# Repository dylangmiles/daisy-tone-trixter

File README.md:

# Tone Trixter — Daisy Seed3

A guitar pedal that makes a piezo pickup sound like a studio microphone — in real time.

**Build log & demos:** [dylangmiles.github.io/tone-trixter](https://dylangmiles.github.io/tone-trixter/)

Piezo pickups are cheap and reliable but have a characteristic harsh, nasal "quack" that EQ alone
can't fix. Tone Trixter applies an **acoustic body impulse response** to the live piezo signal using
FFT convolution, transforming it to match a condenser microphone placed in front of the same guitar.

**Status: the active development path.** The pedal plays — guitar in, DSP chain, SD-loaded IR,
backing tracks, tuner and OLED menu all running on hardware from a 9 V supply. New work happens
here; the [RP2350 build](https://github.com/dylangmiles/pico-tone-trixter) is the V1 prototype that
proved the idea and is still gigging.

---

## Why the Seed3

The V1 measurements kept arriving at the same conclusion: **the analogue front end sets the noise
floor**, not the DSP. The RP2350 build's ES8388 codec was itself a meaningful part of the noise
budget, which made that conclusion hard to test cleanly.

The Seed3's TAC5242 is 32-bit / 192 kHz with a −120 dB floor. The codec effectively stops being a
factor, and the front-end buffer becomes the *only* thing that matters for noise — which is exactly
the question this project turns on. The 480 MHz Cortex-M7 is a bonus rather than the reason.

---

## Hardware

**Processor:** Electrosmith Daisy Seed3 — STM32H750, Cortex-M7 @ 480 MHz, hardware FPU, 64 MB SDRAM
**Codec:** TI TAC5242 — 32-bit / 192 kHz, −120 dB noise floor, hardware-strapped

```
Guitar piezo → buffer daughter board (JFET follower, or OPA1642 op-amp)
  → Seed3 ADC
    → 2048-tap IR convolution (inline) → input trim → 3-band EQ
      → compressor/limiter → output level
    → backing-track mix (after the chain, deliberately)
  → Seed3 DAC → PA / headphones / interface
```

The piezo buffer lives on a swappable 5-pin daughter board, shared with the V1 build. ⚠ **The Seed3
has no input buffer of its own** and its input is line-level, so the high-impedance buffer stage is
mandatory rather than optional.

Built on cut-down perfboard with the Seed under-mounted, 9 V jack power, SH1106 OLED + rotary
encoder, two footswitches (tuner / DSP bypass), and a bit-banged microSD slot.

---

## Features

- **2048-tap IR convolution**, running inline on the M7 — no second core needed
- **DSP chain:** input trim → 3-band EQ (RBJ biquads) → compressor/limiter → output level
- **Presets** bundling all parameters plus IR selection; switching guitars re-stages the whole chain
- **SD card:** drop `tonetrix/` on a card to override presets (`presets.txt`) and add IRs
  (`ir/*.wav`) without reflashing
- **Backing tracks** streamed from the card, mixed *after* the chain so the bed never goes through
  the guitar's IR, EQ or compressor
- **YIN tuner**, full-screen, footswitch-toggled, muting, fed from the raw input
- **OLED home screen:** preset, IR, CPU load, and in / gain-reduction / out meters with a sticky
  clip indicator
- **Live USB-serial control:** every parameter adjustable while playing (`help` lists commands),
  plus timing, CPU and encoder diagnostics

⚠ **Boot is complete passthrough by design.** The pedal always starts transparent, so anything
measured at boot reflects the front end alone with no DSP on top — which matters while the analogue
path is still being characterised.

---

## Measured performance

Steady state, 48 kHz, 64-sample blocks, chain + 2048-tap IR engaged:

| Figure | Reading |
|---|---|
| Audio CPU, bypass | 1 % |
| Audio CPU, chain + IR | **16 % avg, 45 % peak** |
| Foreground loop | 6.6 ms worst, 8 ms period |
| Backing ring | 98–99 %, 0 underruns |
| Block latency | 1.33 ms |

⚠ **Two budgets, and only one is tight.** Audio has ~84 % spare — the foreground is the constrained
side, where a full OLED flush costs ~28 ms. Any optimisation belongs there, not in the audio path.

---

## Build and flash

Requires the ARM GCC toolchain, `dfu-util`, and [libDaisy](https://github.com/electro-smith/libDaisy)
+ [DaisySP](https://github.com/electro-smith/DaisySP).

```sh
make                                          # or: make LIBDAISY_DIR=/path/to/libDaisy
make program-boot                             # ONCE — installs the Daisy bootloader
make program-dfu                              # thereafter
screen /dev/tty.usbmodem* 115200              # console
```

⚠ **libDaisy must be the `seed3-updates` branch, pinned to a commit.** Seed3 support is not on
`main` — a stock libDaisy configures the wrong codec, and an unmerged branch can be force-pushed
underneath you.

⚠ **`APP_TYPE = BOOT_SRAM`.** The STM32H750 has only 128 KB of internal flash and this app does not
fit; it runs from 480 KB of internal SRAM via the Daisy bootloader, which is why `make program-boot`
is a required one-time step.

---

## Notes worth knowing before you read the code

Several things here deliberately do *not* use the obvious library call. Each has a measured reason,
documented at the point of use:

- **Our own SH1106 driver.** libDaisy's OLED transport sends one I²C transaction *per byte* — about
  77 ms per frame. Ours writes a page per transaction and sends only pages that changed.
- **Our own quadrature decode.** libDaisy's `Encoder::Increment()` needs one exact sample pattern
  that a detented PEC11R rarely produces; it works only within a narrow band of turn speeds.
- **Bit-banged SD over SPI.** The Daisy's SDMMC `CMD` pin is wired to ground on this layout, and the
  breakout's pin order matches no hardware SPI instance.
- **`-u _printf_float` in the Makefile.** libDaisy links `--specs=nano.specs`, and newlib-nano omits
  floating-point conversion from `printf` — every `%f` silently prints nothing without it.

`CLAUDE.md` carries the full engineering detail, including the hardware gotchas that cost bench time.

---

## Relationship to the RP2350 build

The two pedals share the analogue front end, the DSP chain design, the IR capture method, and **one
physical SD card** — the card layout lives once, in the
[Pico repo](https://github.com/dylangmiles/pico-tone-trixter), and both firmwares read it.

Driver sources that could reasonably be shared are kept byte-identical between the builds behind
small platform shims, so a protocol or layout fix on either platform applies to both.

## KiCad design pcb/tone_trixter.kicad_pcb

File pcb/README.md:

# Tone Trixter PCB — rev A

KiCad 10 project. **The schematic is GENERATED**: edit `tools/gen_schematic.py`, run it, never hand-edit
`tone_trixter.kicad_sch` (the next run overwrites it). Design intent and every value's reason are in
`private/docs/daisy_pcb_brief_2026-09-16.md`; pin numbers come from `../board.h`.

```
tools/gen_schematic.py          # the source of truth for the schematic
tools/kisch.py, tools/kisym.py  # tiny writer + KiCad-library symbol extractor
tone_trixter.kicad_sch          # generated
tone_trixter.kicad_pro          # project (created once)
TT.kicad_sym, sym-lib-table     # the Daisy Seed3 symbol, built from the pinout CSV
out/schematic.pdf               # review print (netlist.net + 1:1 board prints also in out/)
```

Check: `kicad-cli sch erc tone_trixter.kicad_sch` (only "symbol differs from library" notices expected —
the op-amp and SD symbols are flattened copies) and `kicad-cli sch export netlist`. `gen_schematic.py`
also runs a wire-through-pin check and prints `CHECK:` lines if any wire crosses a pin it should not.

## Layout (started 2026-10-09)

⚠ **`../enclosure/enclosure.py` is the SINGLE SOURCE OF TRUTH for panel-part positions** (2026-10-12;
enclosure tooling moved to a sibling `enclosure/` dir 2026-10-31). The paper template
(`../enclosure/tools/gen_template.py`) imports it, so the template and the board **cannot drift** —
change a position once, re-render, both follow. Convention locked there: **INPUT on the RIGHT,
OUTPUT on the LEFT** (signal R→L), encoder right of the centred screen.

The enclosure mock-up revised the brief's board envelope. **Current geometry** (see
`../enclosure/enclosure.py`, `../enclosure/tools/gen_template.py` + `gen_side_elevation.py`, rendered
in `../enclosure/out/`):

- 1590XX **landscape** (internal top-face plane 138 × 114, **2.33 mm walls**, internal cavity **33 mm**
  tall, Ø7 corner bosses). All measured off the box 2026-10-10.
- **Full-width board ~132 × 57 mm**, hugging the **back wall**, rear corners notched **10 × 10** for the
  bosses (Ø7 post → 3 mm play). Mounted high under the top face (**gap 8.24 mm**, set by the OLED glass
  flush + encoder body clearing); **Seed hangs ~16.5 below**; OLED + encoder reach up (screen centred on
  the board, toward the rear); footswitches panel-mounted up front at 90 mm centres.
- **TRS + DC jacks bottom-mounted** (barrel 12.4 below the board → axis **~33 % up the wall, lower
  third**, z ≈ 10.8), legs up through the PCB, isolated plastic bushings. **USB = Seed's own port** on a
  flexible extender. **Two high-Z inputs drilled in v1** — IN A (AIN1) + IN B (AIN2), both K3599 TRS;
  the XLR mic reserve is dropped (a v2 board).
- ✅ All Z-stack heights (OLED/encoder/Seed/jack/cavity) **measured** 2026-10-10; see the side-elevation.
- The mock-up is an **OUTSIDE drilling template** (tape outside, ink up, drill from outside; register by
  the box **centre** — mark the diagonals). The rear-wall strip is **mirrored** (drawn as seen from
  behind the pedal). For board-mounted jacks the most accurate method is to drill through the finished board.

**Assembly plan (decided 2026-10-15):** **0805** passives (kept over 0603 for hand-reworkability).
**JLC assembles the SMD** — **single-side on B.Cu** (all 112 SMDs under the board — bottom-lid
debug access; validated 0 on F.Cu 2026-10-31), prefer JLC Basic parts (small
Extended fee for the OPA1642 etc.); parts are LCSC-coded in `gen_schematic.py`. **Hand-solder the
through-hole** — jacks, encoder, Seed, footswitch/battery/DC connectors, test points. For the order,
export Gerbers + BOM + CPL from KiCad. Finish = **ENIG** (flatter pads for assembly). See brief §4.

**The outline is GENERATED** — `tools/gen_board.py` (run with KiCad's bundled python; has `pcbnew`):

```
/Applications/KiCad/KiCad.app/Contents/Frameworks/Python.framework/Versions/Current/bin/python3 \
    tools/gen_board.py          # writes tone_trixter.kicad_pcb: Edge.Cuts outline + M3 holes only
```

Then in KiCad: open `tone_trixter.kicad_pcb`, **Tools → Update PCB from Schematic (F8)** to pull in
the 102 footprints (the schematic has them all assigned), place per the mock-up, route, DRC, 3D-check
against the box height, Gerbers. One plane (bottom pour), star at power entry; no copper within 1 mm
of the edge; mounting holes become plane-bonded once the enclosure bond is finalised.

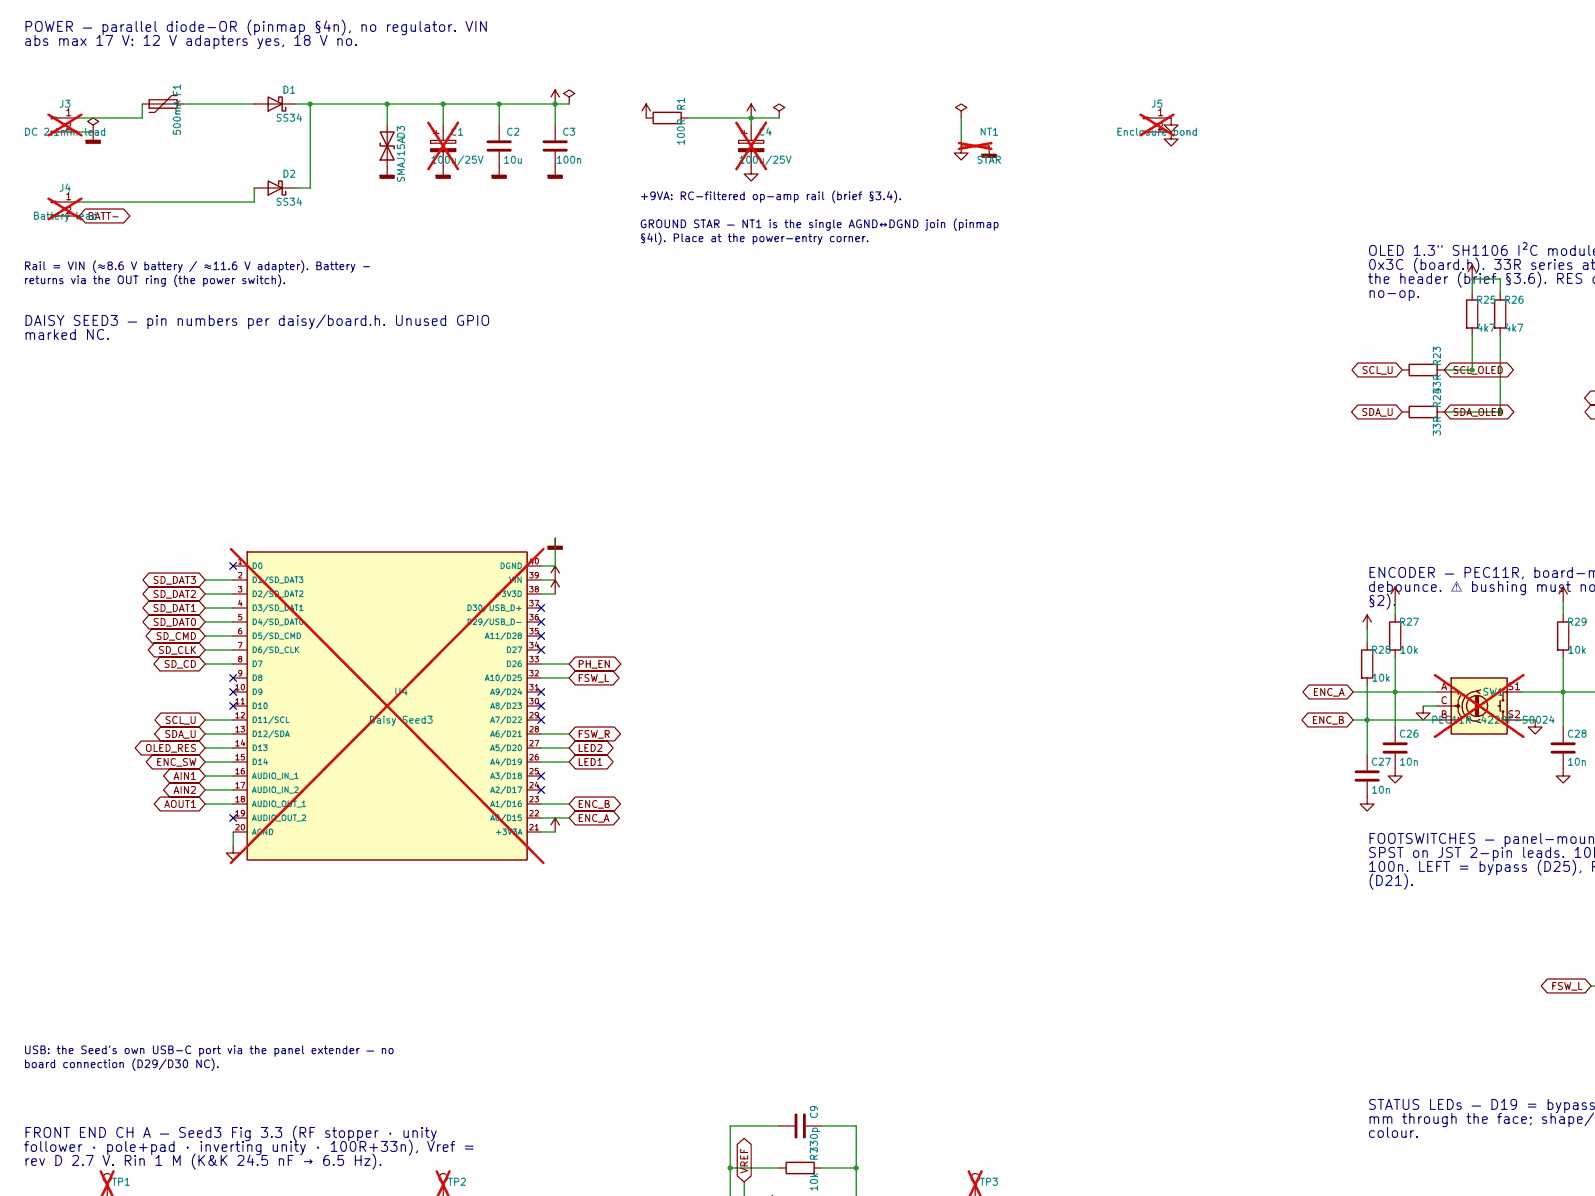
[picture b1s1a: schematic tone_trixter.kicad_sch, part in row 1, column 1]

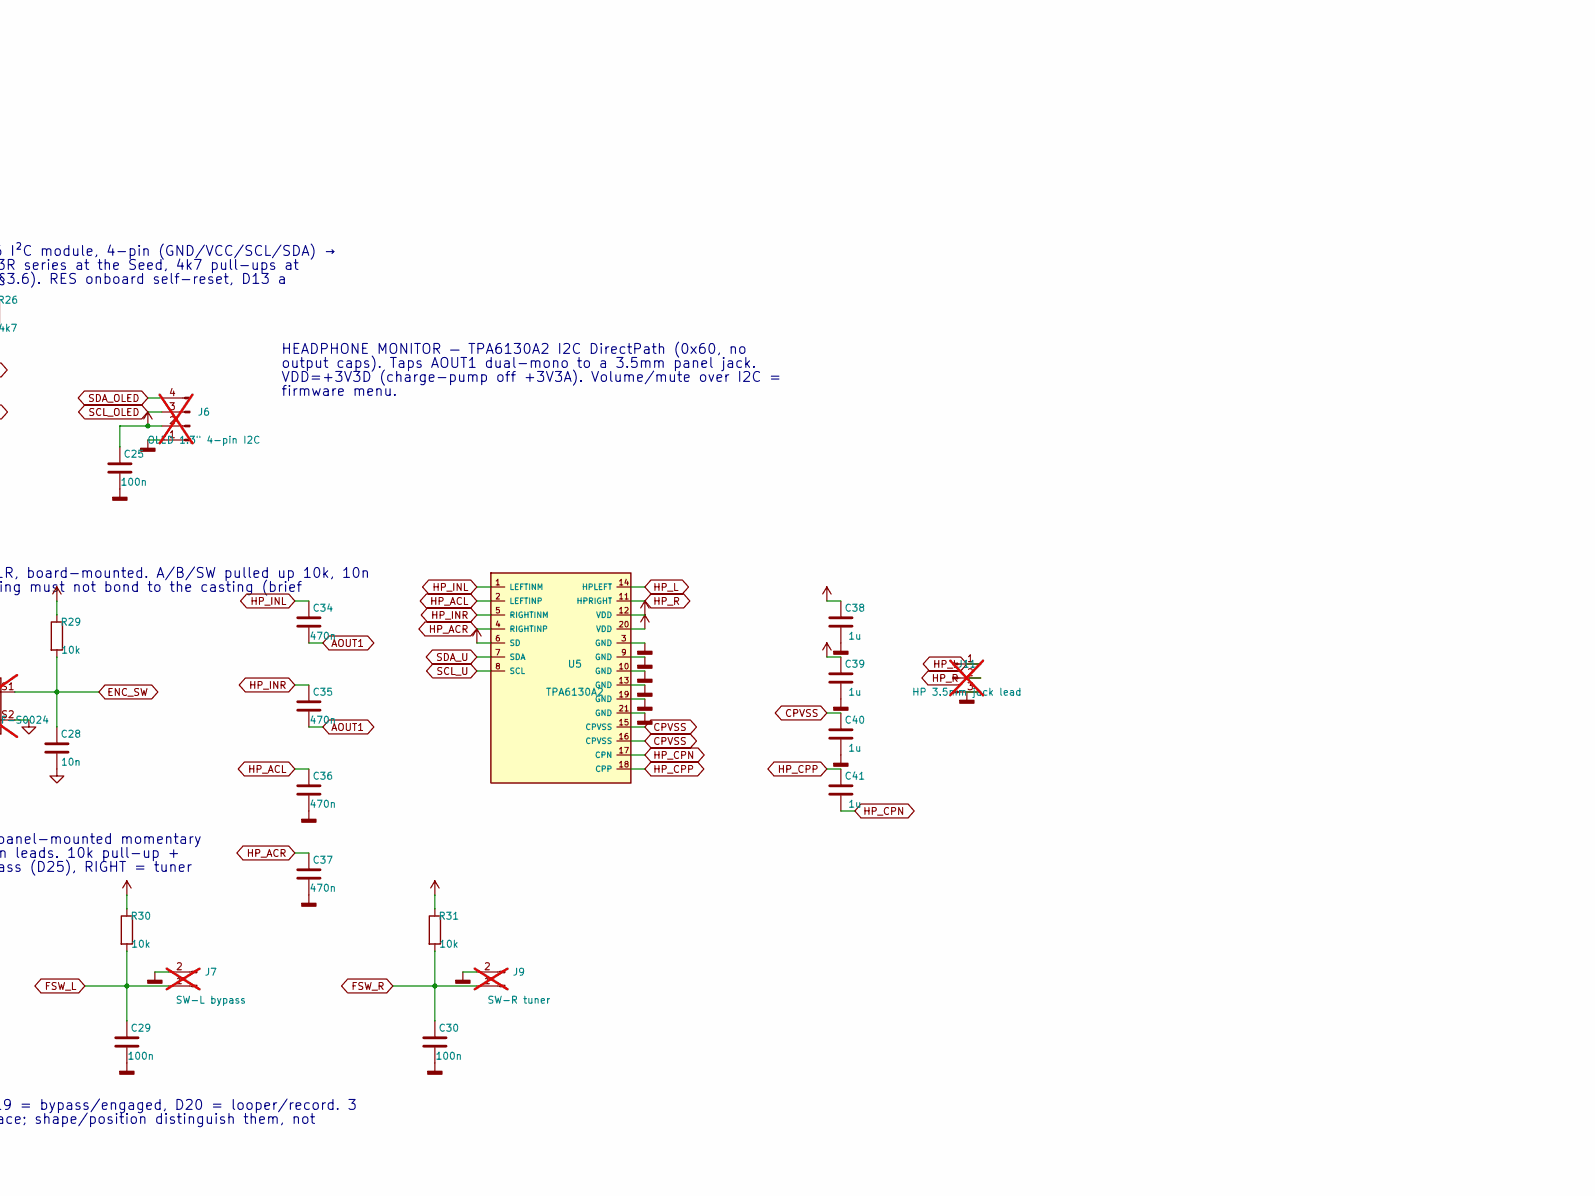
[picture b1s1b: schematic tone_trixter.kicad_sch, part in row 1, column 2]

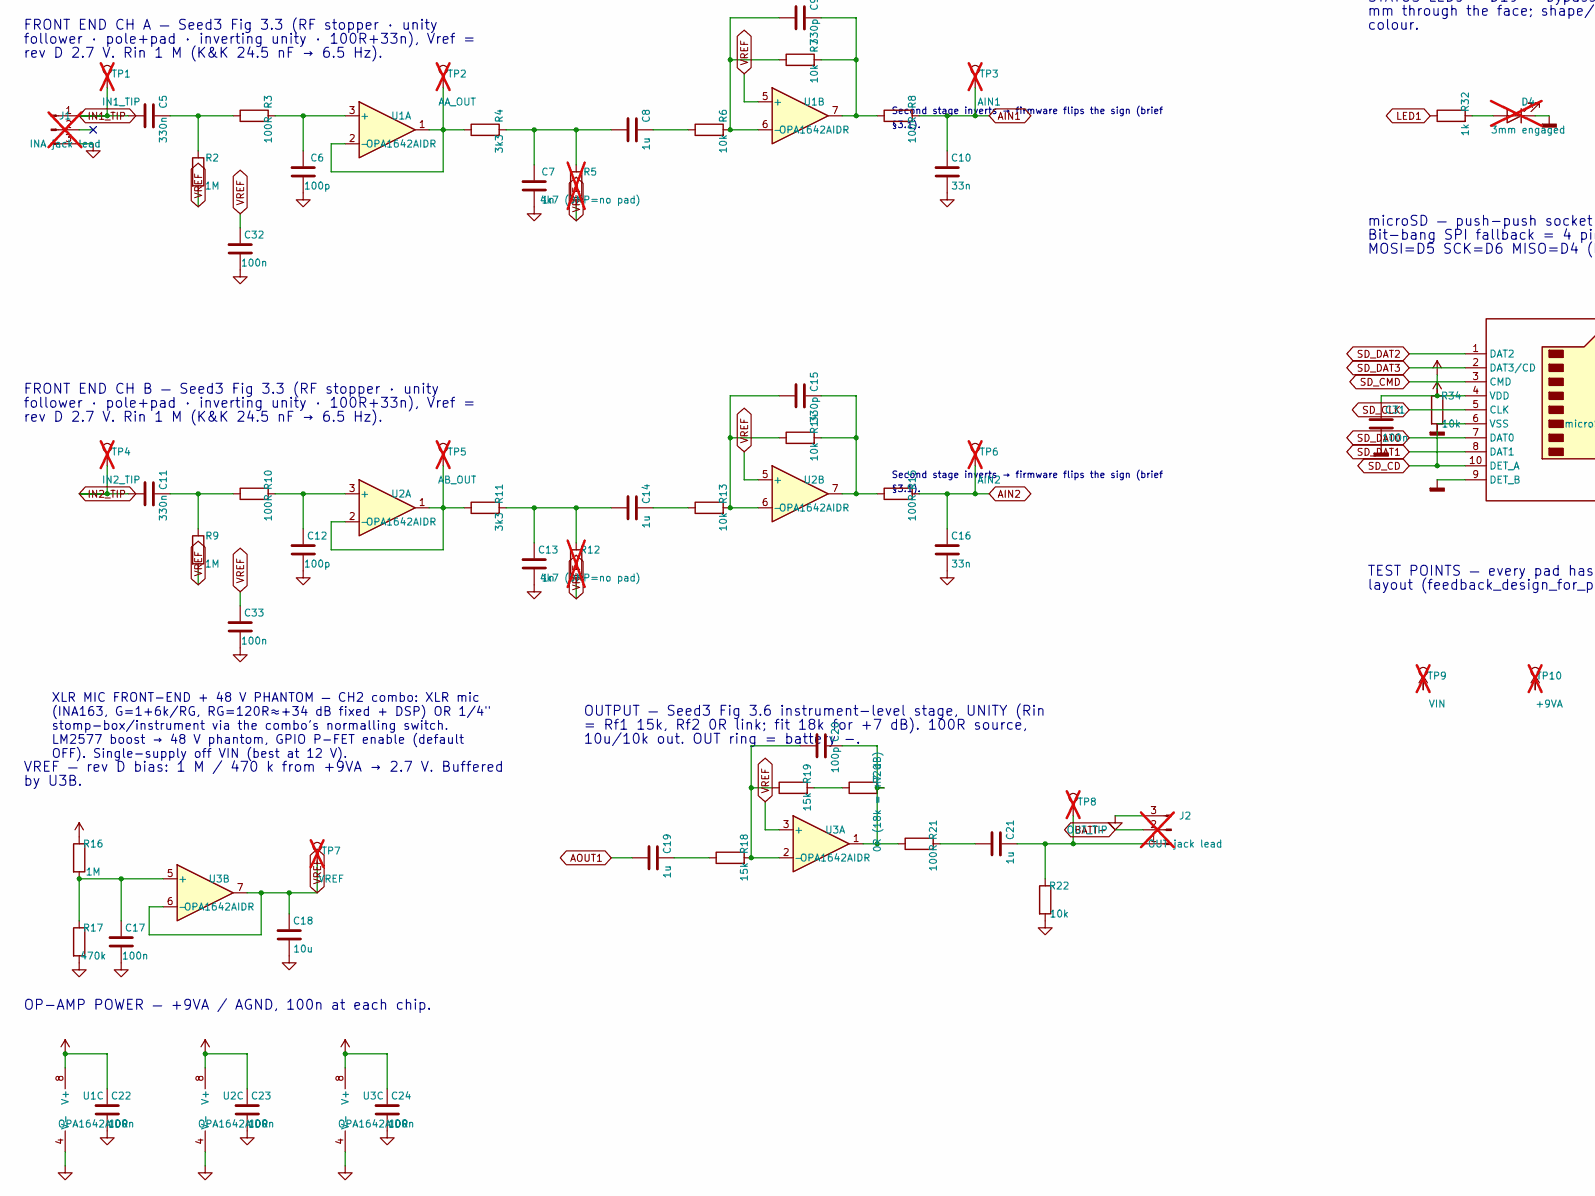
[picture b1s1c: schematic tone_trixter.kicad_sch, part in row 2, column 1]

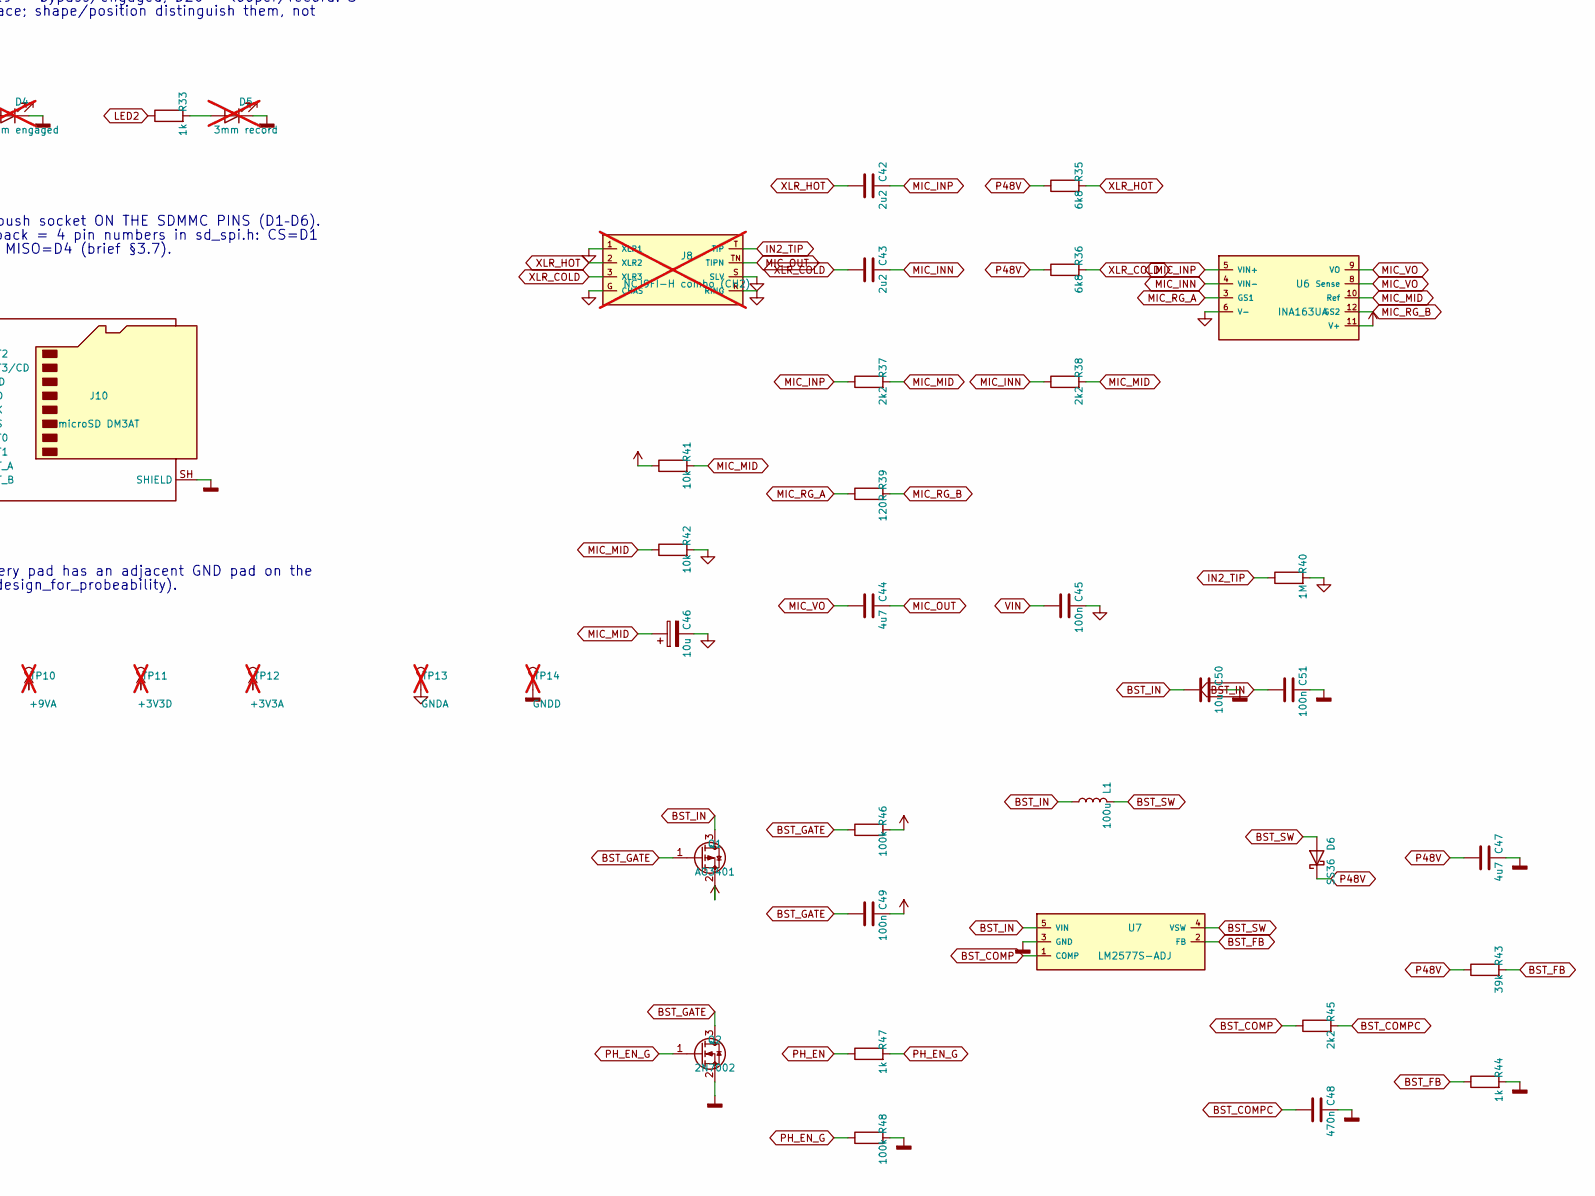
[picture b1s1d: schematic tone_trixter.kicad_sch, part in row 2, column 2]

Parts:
C1, C4: 100u/25V; CP_Radial_D6.3mm_P2.50mm; not fitted
C2, C18: 10u; C_0805_2012Metric
C3, C17, C22, C23, C24, C25, C29, C30, C31, C32, C33, C45, C49, C51: 100n; C_0805_2012Metric
C5, C11: 330n; C_0805_2012Metric
C6, C12, C20: 100p; C_0805_2012Metric
C7, C13: 1n; C_0805_2012Metric
C8, C14, C19, C21: 1u; C_1210_3225Metric
C9, C15: 330p; C_0805_2012Metric
C10, C16: 33n; C_0805_2012Metric
C26, C27, C28: 10n; C_0805_2012Metric
C34, C35, C36, C37, C48: 470n; C_0805_2012Metric
C38, C39, C40, C41: 1u; C_0805_2012Metric
C42, C43: 2u2; C_1210_3225Metric
C44, C47: 4u7; C_1210_3225Metric
C46, C50: 10u; C_1210_3225Metric
D1, D2: SS34; D_SMA; LCSC C8678
D3: SMAJ15A; D_SMA; LCSC C86819
D4: 3mm engaged; LED_D3.0mm; not fitted
D5: 3mm record; LED_D3.0mm; not fitted
D6: SS36; D_SMA; LCSC C16015
F1: 500mA; Fuse_1812_4532Metric; LCSC C883141
J1: INA jack lead; K3599_TRS_6leg; not fitted
J2: OUT jack lead; K3599_TRS_6leg; not fitted
J3: DC 2.1mm lead; JST_XH_B2B-XH-A_1x02_P2.50mm_Vertical; not fitted
J4: Battery lead; JST_XH_B2B-XH-A_1x02_P2.50mm_Vertical; not fitted
J5: Enclosure bond; JST_XH_B2B-XH-A_1x02_P2.50mm_Vertical; not fitted
J6: OLED 1.3" 4-pin I2C; PinHeader_1x04_P2.54mm_Horizontal; not fitted
J7: SW-L bypass; JST_XH_B2B-XH-A_1x02_P2.50mm_Vertical; not fitted
J8: NCJ9FI-H combo (CH2); Jack_XLR-6.35mm_Neutrik_NCJ9FI-H_Horizontal; LCSC C368504; not fitted
J9: SW-R tuner; JST_XH_B2B-XH-A_1x02_P2.50mm_Vertical; not fitted
J10: microSD DM3AT; microSD_HC_Hirose_DM3AT-SF-PEJM5; LCSC C114218
J11: HP 3.5mm jack lead; JST_XH_B3B-XH-A_1x03_P2.50mm_Vertical; not fitted
L1: 100u; L_12x12mm_H8mm; LCSC C169378
NT1: STAR; NetTie-2_SMD_Pad0.5mm; not fitted
Q1: AO3401; SOT-23; LCSC C15127
Q2: 2N7002; SOT-23; LCSC C8545
R1, R3, R8, R10, R15, R21: 100R; R_0805_2012Metric
R2, R9, R16, R40: 1M; R_0805_2012Metric
R4, R11: 3k3; R_0805_2012Metric
R5, R12: 4k7 (DNP=no pad); R_0805_2012Metric; not fitted
R6, R7, R13, R14, R22, R27, R28, R29, R30, R31, R34, R41, R42: 10k; R_0805_2012Metric
R17: 470k; R_0805_2012Metric
R18, R19: 15k; R_0805_2012Metric
R20: 0R (18k = +7 dB); R_0805_2012Metric
R23, R24: 33R; R_0805_2012Metric
R25, R26: 4k7; R_0805_2012Metric
R32, R33, R44, R47: 1k; R_0805_2012Metric
R35, R36: 6k8; R_0805_2012Metric
R37, R38, R45: 2k2; R_0805_2012Metric
R39: 120R; R_0805_2012Metric
R43: 39k; R_0805_2012Metric
R46, R48: 100k; R_0805_2012Metric
SW1: PEC11R-4220F-S0024; RotaryEncoder_Alps_EC11E-Switch_Vertical_H20mm_CircularMoun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; not fitted
TP1: IN1_TIP; TestPoint_Pad_D1.5mm; not fitted
TP2: AA_OUT; TestPoint_Pad_D1.5mm; not fitted
TP3: AIN1; TestPoint_Pad_D1.5mm; not fitted
TP4: IN2_TIP; TestPoint_Pad_D1.5mm; not fitted
TP5: AB_OUT; TestPoint_Pad_D1.5mm; not fitted
TP6: AIN2; TestPoint_Pad_D1.5mm; not fitted
TP7: VREF; TestPoint_Pad_D1.5mm; not fitted
TP8: OUT_TIP; TestPoint_Pad_D1.5mm; not fitted
TP9: VIN; TestPoint_Pad_D1.5mm; not fitted
TP10: +9VA; TestPoint_Pad_D1.5mm; not fitted
TP11: +3V3D; TestPoint_Pad_D1.5mm; not fitted
TP12: +3V3A; TestPoint_Pad_D1.5mm; not fitted
TP13: GNDA; TestPoint_Pad_D1.5mm; not fitted
TP14: GNDD; TestPoint_Pad_D1.5mm; not fitted
U1, U2, U3: OPA1642AIDR; SOIC-8_3.9x4.9mm_P1.27mm; LCSC C67640
U4: Daisy Seed3; Electrosmith_Daisy_Seed; not fitted
U5: TPA6130A2; QFN-20-1EP_4x4mm_P0.5mm_EP2.5x2.5mm; LCSC C130046
U6: INA163UA; SOIC-14_3.9x8.7mm_P1.27mm; LCSC C962542
U7: LM2577S-ADJ; TO-263-5_TabPin3; LCSC C5122561

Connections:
+3V3A: R27.1, R28.1, R29.1, TP12.1 (1_1), U4.21 (+3V3A)
+3V3D: C25.1, C31.1, C38.1, C39.1, J6.2, J10.4 (VDD), R25.1, R26.1, R30.1, R31.1, R34.1, TP11.1 (1_1), U4.38 (+3V3D), U5.6 (SD), U5.12 (VDD), U5.20 (VDD)
+9VA: C4.1, C22.1, C23.1, C24.1, R1.2, R16.1, TP10.1 (1_1), U1.8 (V+), U2.8 (V+), U3.8 (V+)
AIN1: C10.1, R8.2, TP3.1 (1_1), U4.16 (AUDIO_IN_1)
AIN2: C16.1, R15.2, TP6.1 (1_1), U4.17 (AUDIO_IN_2)
AOUT1: C19.1, C34.2, C35.2, U4.18 (AUDIO_OUT_1)
BATT-: J2.2, J4.2
BST_COMP: R45.1, U7.1 (COMP)
BST_COMPC: C48.1, R45.2
BST_FB: R43.2, R44.1, U7.2 (FB)
BST_GATE: C49.1, Q1.1 (G), Q2.3 (D), R46.1
BST_IN: C50.1, C51.1, L1.1, Q1.3 (D), U7.5 (VIN)
BST_SW: D6.2 (A), L1.2, U7.4 (VSW)
CPVSS: C40.1, U5.15 (CPVSS), U5.16 (CPVSS)
ENC_A: C26.1, R27.2, SW1.A, U4.22 (A0/D15)
ENC_B: C27.1, R28.2, SW1.B, U4.23 (A1/D16)
ENC_SW: C28.1, R29.2, SW1.S1, U4.15 (D14)
FSW_L: C29.1, J7.1, R30.2, U4.32 (A10/D25)
FSW_R: C30.1, J9.1, R31.2, U4.28 (A6/D21)
GNDA: C4.2, C6.2, C7.2, C10.2, C12.2, C13.2, C16.2, C17.2, C18.2, C22.2, C23.2, C24.2, C26.2, C27.2, C28.2, C32.2, C33.2, C45.2, C46.2, J1.3, J2.3, J5.1, J5.2, J8.1 (XLR1), J8.G (CHAS), J8.R (RING), J8.S (SLV), NT1.1, R17.2, R22.2, R40.2, R42.2, SW1.C, SW1.S2, TP13.1 (1_1), U1.4 (V-), U2.4 (V-), U3.4 (V-), U4.20 (AGND), U6.6 (V-)
GNDD: C1.2, C2.2, C3.2, C25.2, C29.2, C30.2, C31.2, C36.2, C37.2, C38.2, C39.2, C40.2, C47.2, C48.2, C50.2, C51.2, D3.1 (A1), D4.1 (K), D5.1 (K), J3.2, J6.1, J7.2, J9.2, J10.6 (VSS), J10.9 (DET_B), J10.SH (SHIELD), J11.3, NT1.2, Q2.2 (S), R44.2, R48.2, TP14.1 (1_1), U4.40 (DGND), U5.3 (GND), U5.9 (GND), U5.10 (GND), U5.13 (GND), U5.19 (GND), U5.21 (GND), U7.3 (GND)
HP_ACL: C36.1, U5.2 (LEFTINP)
HP_ACR: C37.1, U5.4 (RIGHTINP)
HP_CPN: C41.2, U5.17 (CPN)
HP_CPP: C41.1, U5.18 (CPP)
HP_INL: C34.1, U5.1 (LEFTINM)
HP_INR: C35.1, U5.5 (RIGHTINM)
HP_L: J11.1, U5.14 (HPLEFT)
HP_R: J11.2, U5.11 (HPRIGHT)
IN1_TIP: C5.1, J1.1, TP1.1 (1_1)
IN2_TIP: C11.1, J8.T (TIP), R40.1, TP4.1 (1_1)
LED1: R32.1, U4.26 (A4/D19)
LED2: R33.1, U4.27 (A5/D20)
MIC_INN: C43.2, R38.1, U6.4 (VIN-)
MIC_INP: C42.2, R37.1, U6.5 (VIN+)
MIC_MID: C46.1, R37.2, R38.2, R41.2, R42.1, U6.10 (Ref)
MIC_OUT: C44.2, J8.TN (TIPN)
MIC_RG_A: R39.1, U6.3 (GS1)
MIC_RG_B: R39.2, U6.12 (GS2)
MIC_VO: C44.1, U6.8 (Sense), U6.9 (VO)
unnamed: C5.2, R2.1, R3.1
unnamed: C7.1, C8.1, R4.2, R5.1
unnamed: C8.2, R6.1
unnamed: C9.2, R7.2, R8.1, U1.7
unnamed: C11.2, R9.1, R10.1
unnamed: C13.1, C14.1, R11.2, R12.1
unnamed: C14.2, R13.1
unnamed: C15.2, R14.2, R15.1, U2.7
unnamed: C19.2, R18.1
unnamed: C20.2, R20.2, R21.1, U3.1
unnamed: C21.1, R21.2
unnamed: D1.2 (A), F1.2
unnamed: D2.2 (A), J4.1
unnamed: D4.2 (A), R32.2
unnamed: D5.2 (A), R33.2
unnamed: C21.2, J2.1, R22.1, TP8.1 (1_1)
unnamed: F1.1, J3.1
unnamed: R19.2, R20.1
unnamed: C6.1, R3.2, U1.3 (+)
unnamed: R4.1, TP2.1 (1_1), U1.1, U1.2 (-)
unnamed: C9.1, R6.2, R7.1, U1.6 (-)
unnamed: C12.1, R10.2, U2.3 (+)
unnamed: R11.1, TP5.1 (1_1), U2.1, U2.2 (-)
unnamed: C15.1, R13.2, R14.1, U2.6 (-)
unnamed: C20.1, R18.2, R19.1, U3.2 (-)
unnamed: C17.1, R16.2, R17.1, U3.5 (+)
OLED_RES: U4.14 (D13)
P48V: C47.1, D6.1 (K), R35.1, R36.1, R43.1
PH_EN: R47.1, U4.33 (D26)
PH_EN_G: Q2.1 (G), R47.2, R48.1
SCL_OLED: J6.3, R23.2, R25.2
SCL_U: R23.1, U4.12 (D11/SCL), U5.8 (SCL)
SDA_OLED: J6.4, R24.2, R26.2
SDA_U: R24.1, U4.13 (D12/SDA), U5.7 (SDA)
SD_CD: J10.10 (DET_A), R34.2, U4.8 (D7)
SD_CLK: J10.5 (CLK), U4.7 (D6/SD_CLK)
SD_CMD: J10.3 (CMD), U4.6 (D5/SD_CMD)
SD_DAT0: J10.7 (DAT0), U4.5 (D4/SD_DAT0)
SD_DAT1: J10.8 (DAT1), U4.4 (D3/SD_DAT1)
SD_DAT2: J10.1 (DAT2), U4.3 (D2/SD_DAT2)
SD_DAT3: J10.2 (DAT3/CD), U4.2 (D1/SD_DAT3)
VIN: C1.1, C2.1, C3.1, C45.1, C49.2, D1.1 (K), D2.1 (K), D3.2 (A2), Q1.2 (S), R1.1, R41.1, R46.2, TP9.1 (1_1), U4.39 (VIN), U6.11 (V+)
VREF: C18.1, C32.1, C33.1, R2.2, R5.2, R9.2, R12.2, TP7.1 (1_1), U1.5 (+), U2.5 (+), U3.3 (+), U3.6 (-), U3.7
XLR_COLD: C43.1, J8.3 (XLR3), R36.2
XLR_HOT: C42.1, J8.2 (XLR2), R35.2

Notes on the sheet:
POWER — parallel diode-OR (pinmap §4n), no regulator. VIN
abs max 17 V: 12 V adapters yes, 18 V no.
Rail = VIN (≈8.6 V battery / ≈11.6 V adapter). Battery −
returns via the OUT ring (the power switch).
+9VA: RC-filtered op-amp rail (brief §3.4).
GROUND STAR — NT1 is the single AGND↔DGND join (pinmap
§4l). Place at the power-entry corner.
DAISY SEED3 — pin numbers per daisy/board.h. Unused GPIO
marked NC.
USB: the Seed's own USB-C port via the panel extender — no
board connection (D29/D30 NC).
FRONT END CH A — Seed3 Fig 3.3 (RF stopper · unity
follower · pole+pad · inverting unity · 100R+33n), Vref =
rev D 2.7 V. Rin 1 M (K&K 24.5 nF → 6.5 Hz).
Second stage inverts → firmware flips the sign (brief
§3.1).
FRONT END CH B — Seed3 Fig 3.3 (RF stopper · unity
VREF — rev D bias: 1 M / 470 k from +9VA → 2.7 V. Buffered
by U3B.
OUTPUT — Seed3 Fig 3.6 instrument-level stage, UNITY (Rin
= Rf1 15k, Rf2 0R link; fit 18k for +7 dB). 100R source,
10u/10k out. OUT ring = battery −.
OP-AMP POWER — +9VA / AGND, 100n at each chip.
OLED 1.3" SH1106 I²C module, 4-pin (GND/VCC/SCL/SDA) →
0x3C (board.h). 33R series at the Seed, 4k7 pull-ups at
the header (brief §3.6). RES onboard self-reset, D13 a
no-op.
ENCODER — PEC11R, board-mounted. A/B/SW pulled up 10k, 10n
debounce. ⚠ bushing must not bond to the casting (brief
§2).
FOOTSWITCHES — panel-mounted momentary
SPST on JST 2-pin leads. 10k pull-up +
100n. LEFT = bypass (D25), RIGHT = tuner
(D21).
STATUS LEDs — D19 = bypass/engaged, D20 = looper/record. 3
mm through the face; shape/position distinguish them, not
colour.
microSD — push-push socket ON THE SDMMC PINS (D1–D6).
Bit-bang SPI fallback = 4 pin numbers in sd_spi.h: CS=D1
MOSI=D5 SCK=D6 MISO=D4 (brief §3.7).

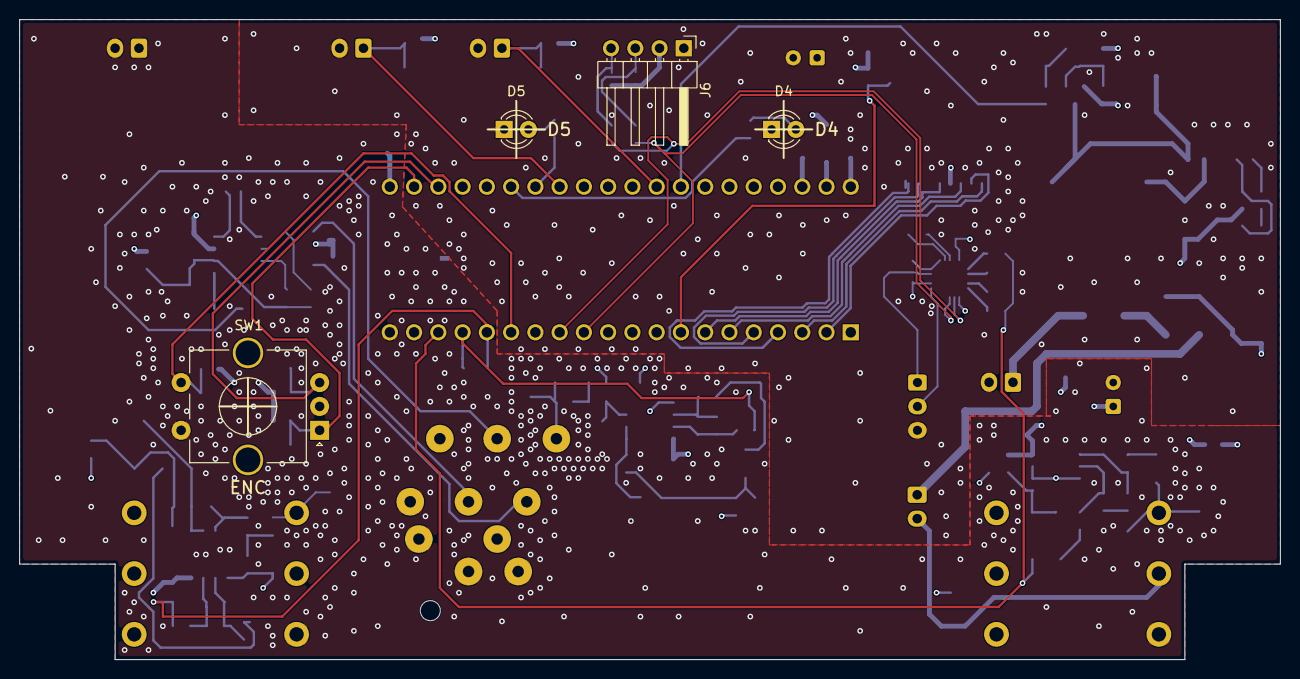
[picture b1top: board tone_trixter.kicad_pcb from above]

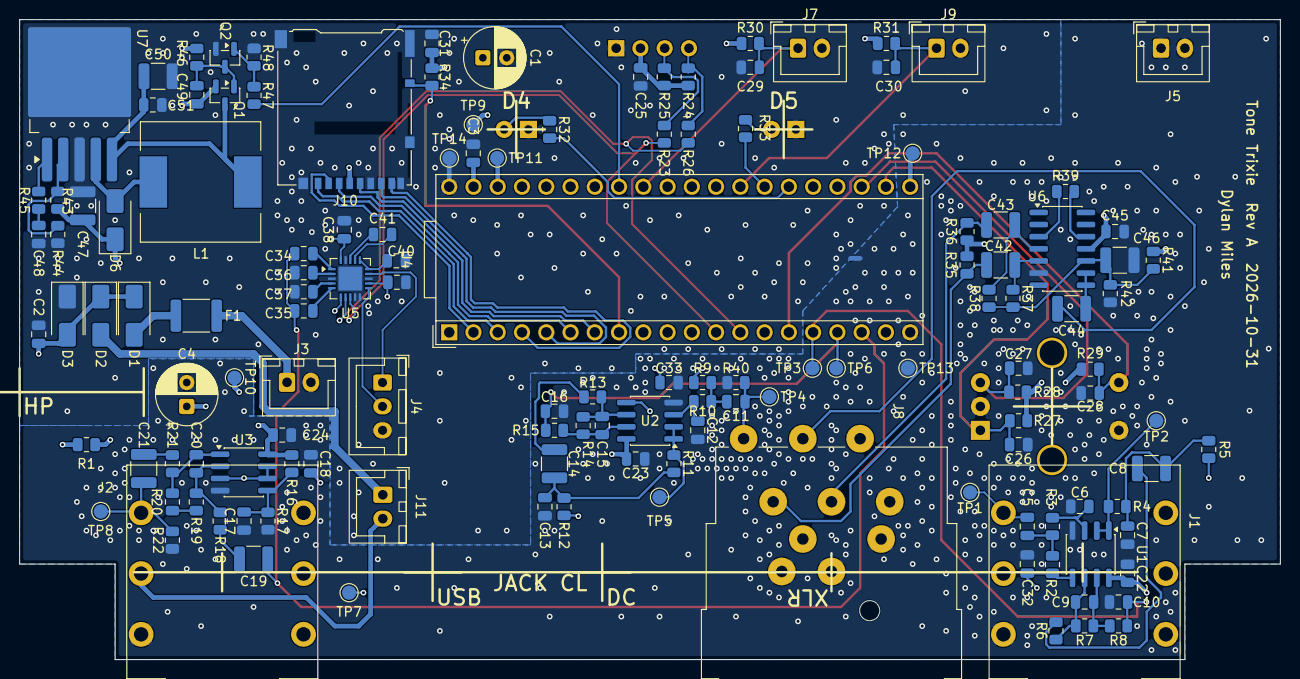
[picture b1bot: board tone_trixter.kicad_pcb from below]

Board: 4 copper layers, 132.0 x 67.0 mm, 143 parts (139 on the bottom side), 84 nets.

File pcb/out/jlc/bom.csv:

"Comment","Designator","Footprint","LCSC","Quantity"
"100u/25V","C1,C4","Capacitor_THT:CP_Radial_D6.3mm_P2.50mm","","2"
"10u","C2,C18","Capacitor_SMD:C_0805_2012Metric","","2"
"100n","C3,C17,C22-C25,C29-C33,C45,C49,C51","Capacitor_SMD:C_0805_2012Metric","","14"
"330n","C5,C11","Capacitor_SMD:C_0805_2012Metric","","2"
"100p","C6,C12,C20","Capacitor_SMD:C_0805_2012Metric","","3"
"1n","C7,C13","Capacitor_SMD:C_0805_2012Metric","","2"
"1u","C8,C14,C19,C21","Capacitor_SMD:C_1210_3225Metric","","4"
"330p","C9,C15","Capacitor_SMD:C_0805_2012Metric","","2"
"33n","C10,C16","Capacitor_SMD:C_0805_2012Metric","","2"
"10n","C26-C28","Capacitor_SMD:C_0805_2012Metric","","3"
"470n","C34-C37,C48","Capacitor_SMD:C_0805_2012Metric","","5"
"1u","C38-C41","Capacitor_SMD:C_0805_2012Metric","","4"
"2u2","C42,C43","Capacitor_SMD:C_1210_3225Metric","","2"
"4u7","C44,C47","Capacitor_SMD:C_1210_3225Metric","","2"
"10u","C46,C50","Capacitor_SMD:C_1210_3225Metric","","2"
"SS34","D1,D2","Diode_SMD:D_SMA","C8678","2"
"SMAJ15A","D3","Diode_SMD:D_SMA","C129213","1"
"3mm engaged","D4","LED_THT:LED_D3.0mm","","1"
"3mm record","D5","LED_THT:LED_D3.0mm","","1"
"SS36","D6","Diode_SMD:D_SMA","C16015","1"
"500mA","F1","Fuse:Fuse_1812_4532Metric","C883116","1"
"INA jack lead","J1","TT:K3599_TRS_6leg","","1"
"OUT jack lead","J2","TT:K3599_TRS_6leg","","1"
"DC 2.1mm lead","J3","Connector_JST:JST_XH_B2B-XH-A_1x02_P2.50mm_Vertical","","1"
"Battery lead","J4","Connector_JST:JST_XH_B2B-XH-A_1x02_P2.50mm_Vertical","","1"
"Enclosure bond","J5","Connector_JST:JST_XH_B2B-XH-A_1x02_P2.50mm_Vertical","","1"
"OLED 1.3"" 4-pin I2C","J6","Connector_PinHeader_2.54mm:PinHeader_1x04_P2.54mm_Horizontal","","1"
"SW-L bypass","J7","Connector_JST:JST_XH_B2B-XH-A_1x02_P2.50mm_Vertical","","1"
"NCJ9FI-H combo (CH2)","J8","Connector_Audio:Jack_XLR-6.35mm_Neutrik_NCJ9FI-H_Horizontal","C368504","1"
"SW-R tuner","J9","Connector_JST:JST_XH_B2B-XH-A_1x02_P2.50mm_Vertical","","1"
"microSD DM3AT","J10","Connector_Card:microSD_HC_Hirose_DM3AT-SF-PEJM5","C114218","1"
"HP 3.5mm jack lead","J11","Connector_JST:JST_XH_B3B-XH-A_1x03_P2.50mm_Vertical","","1"
"100u","L1","Inductor_SMD:L_12x12mm_H8mm","C169378","1"
"STAR","NT1","NetTie:NetTie-2_SMD_Pad0.5mm","","1"
"AO3401","Q1","Package_TO_SOT_SMD:SOT-23","C15127","1"
"2N7002","Q2","Package_TO_SOT_SMD:SOT-23","C8545","1"
"100R","R1,R3,R8,R10,R15,R21","Resistor_SMD:R_0805_2012Metric","","6"
"1M","R2,R9,R16,R40","Resistor_SMD:R_0805_2012Metric","","4"
"3k3","R4,R11","Resistor_SMD:R_0805_2012Metric","","2"
"10k","R6,R7,R13,R14,R22,R27-R31,R34,R41,R42","Resistor_SMD:R_0805_2012Metric","","13"
"470k","R17","Resistor_SMD:R_0805_2012Metric","","1"
"15k","R18,R19","Resistor_SMD:R_0805_2012Metric","","2"
"0R (18k = +7 dB)","R20","Resistor_SMD:R_0805_2012Metric","","1"
"33R","R23,R24","Resistor_SMD:R_0805_2012Metric","","2"
"4k7","R25,R26","Resistor_SMD:R_0805_2012Metric","","2"
"1k","R32,R33,R44,R47","Resistor_SMD:R_0805_2012Metric","","4"
"6k8","R35,R36","Resistor_SMD:R_0805_2012Metric","","2"
"2k2","R37,R38,R45","Resistor_SMD:R_0805_2012Metric","","3"
"120R","R39","Resistor_SMD:R_0805_2012Metric","","1"
"39k","R43","Resistor_SMD:R_0805_2012Metric","","1"
"100k","R46,R48","Resistor_SMD:R_0805_2012Metric","","2"
"PEC11R-4220F-S0024","SW1","Rotary_Encoder:RotaryEncoder_Alps_EC11E-Switch_Vertical_H20mm_CircularMountingHoles","","1"
"IN1_TIP","TP1","TestPoint:TestPoint_Pad_D1.5mm","","1"
"AA_OUT","TP2","TestPoint:TestPoint_Pad_D1.5mm","","1"
"AIN1","TP3","TestPoint:TestPoint_Pad_D1.5mm","","1"
"IN2_TIP","TP4","TestPoint:TestPoint_Pad_D1.5mm","","1"
"AB_OUT","TP5","TestPoint:TestPoint_Pad_D1.5mm","","1"
"AIN2","TP6","TestPoint:TestPoint_Pad_D1.5mm","","1"
"VREF","TP7","TestPoint:TestPoint_Pad_D1.5mm","","1"
"OUT_TIP","TP8","TestPoint:TestPoint_Pad_D1.5mm","","1"
"VIN","TP9","TestPoint:TestPoint_Pad_D1.5mm","","1"
"+9VA","TP10","TestPoint:TestPoint_Pad_D1.5mm","","1"
"+3V3D","TP11","TestPoint:TestPoint_Pad_D1.5mm","","1"
"+3V3A","TP12","TestPoint:TestPoint_Pad_D1.5mm","","1"
"GNDA","TP13","TestPoint:TestPoint_Pad_D1.5mm","","1"
"GNDD","TP14","TestPoint:TestPoint_Pad_D1.5mm","","1"
"OPA1642AIDR","U1-U3","Package_SO:SOIC-8_3.9x4.9mm_P1.27mm","C126004","3"
"OPA1642AIDR","U1,U3","Package_SO:SOIC-8_3.9x4.9mm_P1.27mm","","2"
"Daisy Seed3","U4","Module:Electrosmith_Daisy_Seed","","1"
"TPA6130A2","U5","Package_DFN_QFN:QFN-20-1EP_4x4mm_P0.5mm_EP2.5x2.5mm","C130046","1"
"INA163UA","U6","Package_SO:SOIC-14_3.9x8.7mm_P1.27mm","C962542","1"
"LM2577S-ADJ","U7","Package_TO_SOT_SMD:TO-263-5_TabPin3","C5122561","1"
